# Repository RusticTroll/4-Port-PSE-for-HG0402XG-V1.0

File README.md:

# 4-Port PSE board for HG0402XG V1.0

I recently purchased [this](https://www.amazon.com/TEROW-2-5G-POE-Multi-Speed-Compatible/dp/B0CGDCBBV3) 2.5G-BaseT/SFP+ "PoE" Switch and was appalled to find out that it does not actually perform PoE classification.
It instead, waits for the resistance that a PD puts on the line, then immediately sends power.
While this may "work" to some extent, it also experiences massive transient current spikes when powering up, which could harm the PD.
It is for this reason that I set out to create a replacement board which is at least better than what was provided.

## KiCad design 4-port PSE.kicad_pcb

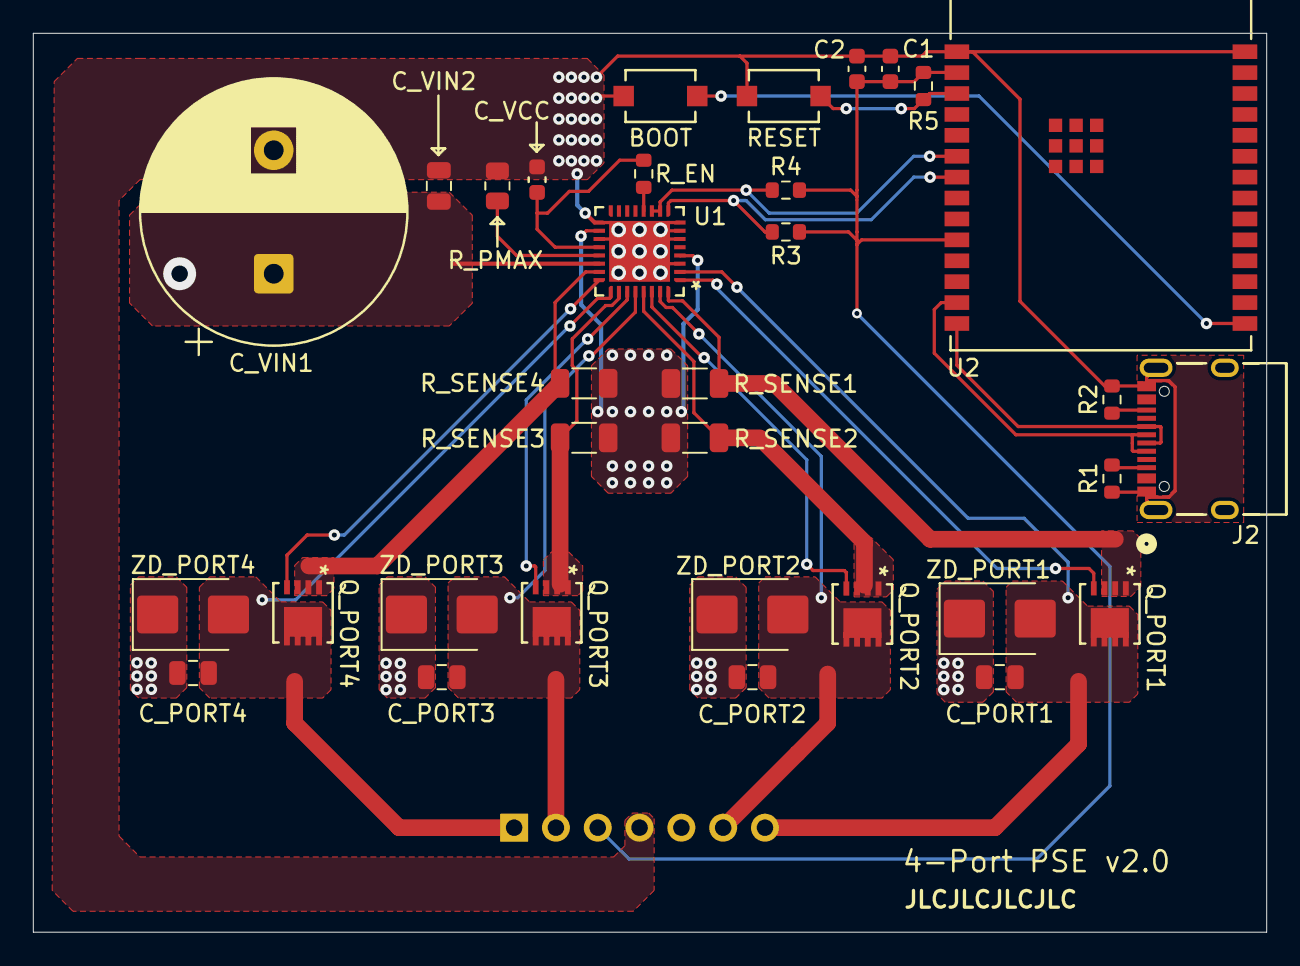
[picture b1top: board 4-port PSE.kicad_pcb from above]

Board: 2 copper layers, 74.9 x 54.6 mm, 34 parts (1 on the bottom side), 26 nets.

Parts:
BOOT: TS-1088-AR02016; SW_TS-1088_XNP
C1: 22µF; C_0603_1608Metric
C2: 0.1µF; C_0603_1608Metric
C_PORT1, C_PORT2, C_PORT3, C_PORT4: 0.1µF; C_0805_2012Metric
C_VCC: 1µF; C_0603_1608Metric
C_VIN1: 220µF; CP_Radial_D16.0mm_P7.50mm
C_VIN2: 0.1µF; C_0805_2012Metric
J1: 1x7 2.54mm PV Female Header; PinSocket_1x07_P2.54mm_Vertical
J2: GT-USB-7004; CONN12_B-7004_GSW
Q_PORT1, Q_PORT2, Q_PORT3, Q_PORT4: FDMC3612; MLP8_3P3X3P3_ONS
R1, R2, R3, R4, R5: 4.7kΩ, ±1%; R_0603_1608Metric
RESET: TS-1088-AR02016; SW_TS-1088_XNP
R_EN: 100kΩ; R_0603_1608Metric
R_PMAX: 75kΩ; R_0805_2012Metric
R_SENSE1, R_SENSE2, R_SENSE3, R_SENSE4: 250mΩ, ±1%, 100V; R_1206_3216Metric
U1: MP3924GU-Z; QFN-32_MP3924_MNP
U2: ESP32-C6-WROOM-1-N8; MOD28_ESP32-C6-WROOM-1_EXP
ZD_PORT1, ZD_PORT2, ZD_PORT3, ZD_PORT4: 58V Vrwm, 95V Vc; D_SMB

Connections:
+3.3V: C1.2, C2.2, J1.3, R3.2, R4.2, R5.2, U2.2 (3V3), U2.10 (IO8)
+52V: C_PORT1.1, C_PORT2.1, C_PORT3.1, C_PORT4.1, C_VIN1.1, C_VIN2.1, J1.5, U1.22 (VIN), ZD_PORT1.1 (K), ZD_PORT2.1 (K), ZD_PORT3.1 (K), ZD_PORT4.1 (K)
DGND: BOOT.2, C1.1, C2.1, C_VCC.1, C_VIN1.2, C_VIN2.2, J1.4, J2.A1 (GND), J2.A12 (GND), J2.B1 (GND), J2.B12 (GND), R1.1, R2.2, RESET.1, R_PMAX.1, R_SENSE1.2, R_SENSE2.2, R_SENSE3.2, R_SENSE4.2, U1.3 (INT2), U1.4 (SGND1), U1.6 (AUTO), U1.7 (MID), U1.8 (INT1), U1.17 (DGND), U1.18 (SGND2), U1.19 (PGND), U2.1 (GND), U2.28 (GND)
N1: C_PORT1.2, J1.7, Q_PORT1.5, Q_PORT1.6, Q_PORT1.7, Q_PORT1.8, U1.2 (OUT1), ZD_PORT1.2 (A)
N2: C_PORT2.2, J1.6, Q_PORT2.5, Q_PORT2.6, Q_PORT2.7, Q_PORT2.8, U1.31 (OUT2), ZD_PORT2.2 (A)
N3: C_PORT3.2, J1.2, Q_PORT3.5, Q_PORT3.6, Q_PORT3.7, Q_PORT3.8, U1.28 (OUT3), ZD_PORT3.2 (A)
N4: C_PORT4.2, J1.1, Q_PORT4.5, Q_PORT4.6, Q_PORT4.7, Q_PORT4.8, U1.25 (OUT4), ZD_PORT4.2 (A)
unnamed: J2.B8 (CC1), R1.2
unnamed: J2.B5 (CC2), R2.1
unnamed: R_EN.2, U1.12 (EN)
unnamed: Q_PORT1.4, U1.1 (GATE1)
unnamed: Q_PORT2.4, U1.30 (GATE2)
unnamed: Q_PORT3.4, U1.27 (GATE3)
unnamed: Q_PORT4.4, U1.24 (GATE4)
unnamed: R_PMAX.2, U1.21 (PMAX)
unnamed: Q_PORT1.1, Q_PORT1.2, Q_PORT1.3, R_SENSE1.1, U1.32 (SENSE1)
unnamed: Q_PORT2.1, Q_PORT2.2, Q_PORT2.3, R_SENSE2.1, U1.29 (SENSE2)
unnamed: Q_PORT3.1, Q_PORT3.2, Q_PORT3.3, R_SENSE3.1, U1.26 (SENSE3)
unnamed: Q_PORT4.1, Q_PORT4.2, Q_PORT4.3, R_SENSE4.1, U1.23 (SENSE4)
unnamed: C_VCC.2, R_EN.1, U1.20 (VCC)
unnamed: R5.1, RESET.2, U2.3 (EN)
unnamed: BOOT.1, U2.15 (IO9)
SCL: R3.1, U1.9 (SCL), U2.7 (IO7)
SDA: R4.1, U1.10 (SDAO), U1.11 (SDAI), U2.6 (IO6)
USB_D+: J2.A6 (D+), J2.B6 (D+), U2.14 (IO13)
USB_D-: J2.A7 (D-), J2.B7 (D-), U2.13 (IO12)

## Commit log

2025-06-19 Initial Commit - V1.0
2025-09-21 Removed README disclaimer on lack of testing
2025-09-21 Moved symbols into their own directory
2025-09-21 Added Symbols/Footprints for ESP32 Module and USB header
2025-11-30 V2.0 - ESP32-C6 controlled
